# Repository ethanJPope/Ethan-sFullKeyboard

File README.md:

# Full Keyboard

My keybaord is a 100% version with a hotswappable pcb with custom USB_C Daughter Board PCB. 

## Why I made this Project
- I want a finished project
- Learn how to make a complex pcb
- Make a full and finished CAD Project

## PCB

**Keyboard PCB**

**USB_C DAUGHTER BOARD**

## CAD

## Final Product

## BOM

| Item | Description         | Unit Price | Supplier   |
|------|---------------------|------------|------------|
| 1    | Custom Keyboard PCB | $55.82     | JLCPCB     |
| 2    | PCB Components      | $22.54     | LCSC       |
| 3    | USB-C Cable         | $6.23      | AliExpress |
| 4    | Hot Swap Sockets    | $6.90      | AliExpress |
| 5    | Stabilizers         | $5.97      | AliExpress |
| 6    | Switches            | $21.65     | AliExpress |
| 7    | Poron Foam          | $5.70      | AliExpress |
| 8    | Keycaps Set         | $19.99     | Amazon     |

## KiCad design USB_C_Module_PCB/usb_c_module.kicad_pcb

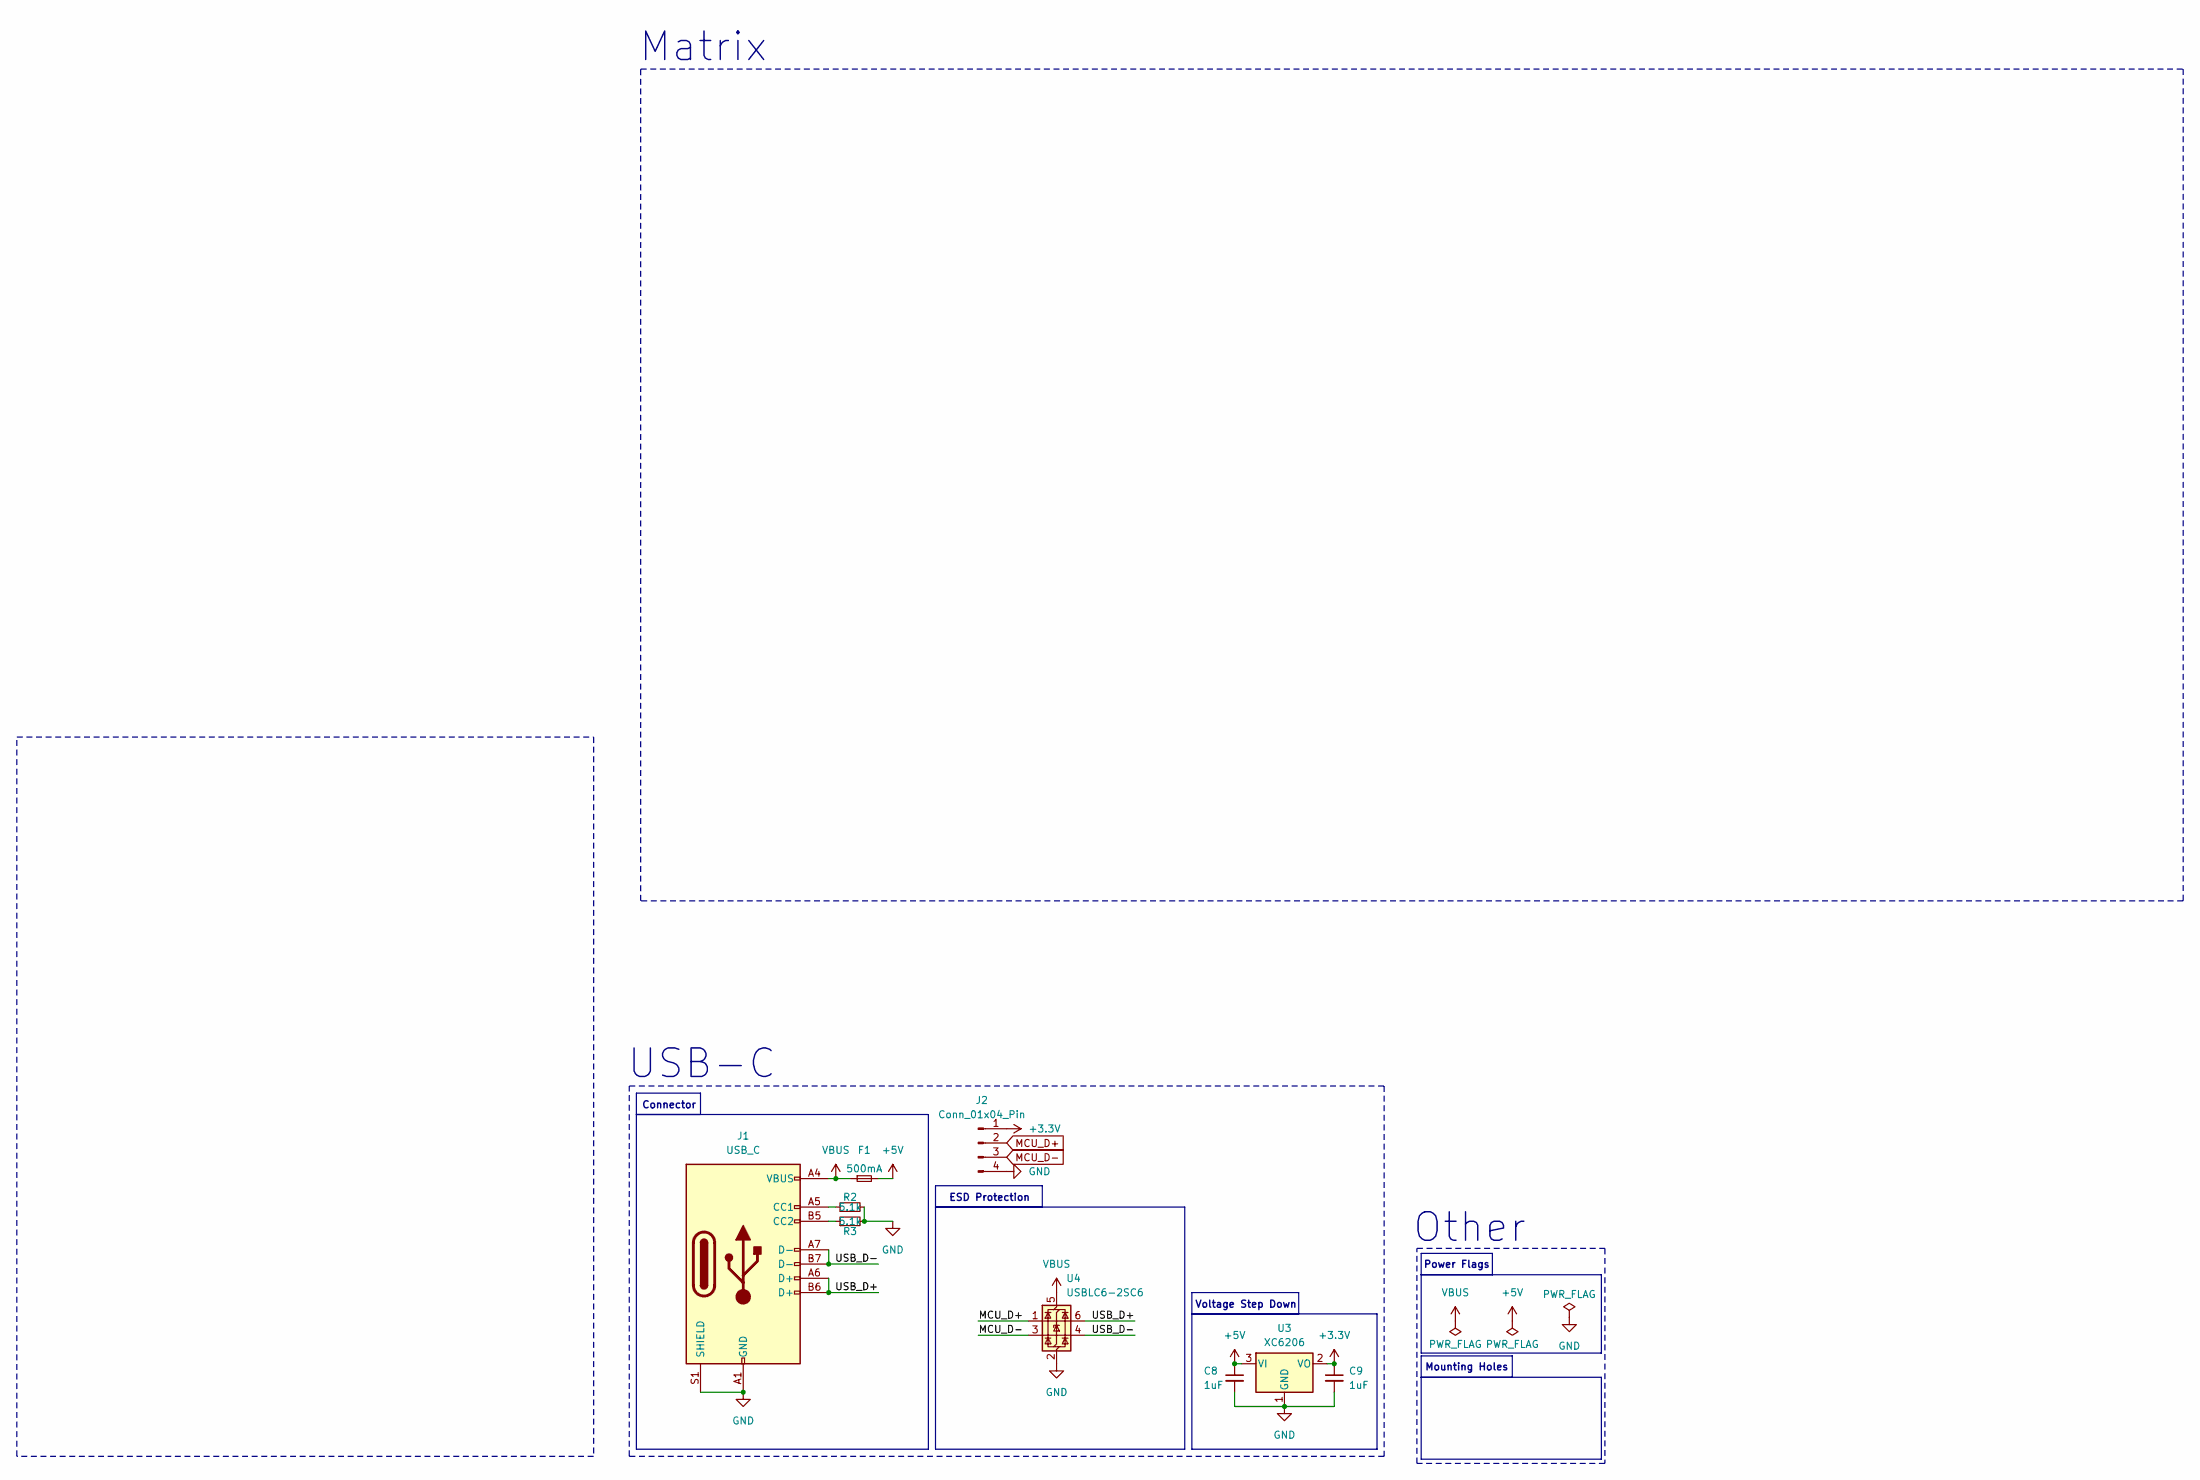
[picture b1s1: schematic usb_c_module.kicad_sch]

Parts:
C8, C9: 1uF; Capacitor_0402; LCSC C52923
F1: 500mA; Fuse_0603; LCSC C210357
J1: USB_C; USB_C_HRO_TYPE-C-31-M-12; LCSC C165948
J2: Conn_01x04_Pin; JST_EH_B4B-EH-A_1x04_P2.50mm_Vertical
R2, R3: 5.1k; Resistor_0402; LCSC C25905
U3: XC6206; Voltage_SOT-23; LCSC C5446
U4: USBLC6-2SC6; ESD_SOT-23-6; LCSC C2827654

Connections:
+3.3V: C9.1, J2.1, U3.2 (VO)
+5V: C8.1, F1.2, U3.3 (VI)
/USB_D+: J1.A6 (D+), J1.B6 (D+), U4.6 (I/O1)
/USB_D-: J1.A7 (D-), J1.B7 (D-), U4.4 (I/O2)
GND: C8.2, C9.2, J1.A1 (GND), J1.A12 (GND), J1.B1 (GND), J1.B12 (GND), J1.S1 (SHIELD), J2.4, R2.2, R3.2, U3.1 (GND), U4.2 (GND)
MCU_D+: J2.2, U4.1 (I/O1)
MCU_D-: J2.3, U4.3 (I/O2)
unnamed: J1.A5 (CC1), R2.1
unnamed: J1.B5 (CC2), R3.1
VBUS: F1.1, J1.A4 (VBUS), J1.A9 (VBUS), J1.B4 (VBUS), J1.B9 (VBUS), U4.5 (VBUS)

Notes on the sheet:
USB-C
Mounting Holes
ESD Protection
Power Flags
Voltage Step Down
Other
Matrix
Connector

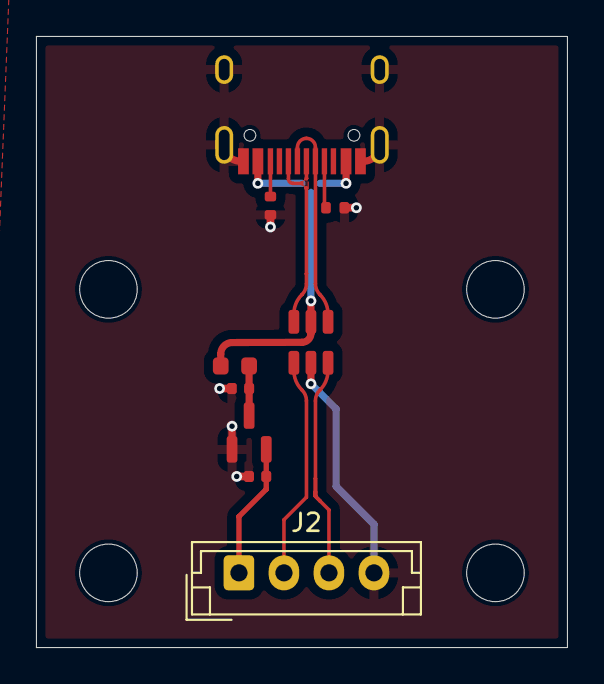
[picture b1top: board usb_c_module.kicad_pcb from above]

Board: 4 copper layers, 29.5 x 34.0 mm, 9 parts (0 on the bottom side), 10 nets.

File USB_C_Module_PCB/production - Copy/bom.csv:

Designator,Footprint,Quantity,Value,LCSC Part #
"C8, C9",Capacitor_0402,2,1uF,C52923
F1,Fuse_0603,1,500mA,C210357
J1,USB_C_HRO_TYPE-C-31-M-12,1,USB_C,C165948
J2,JST_EH_B4B-EH-A_1x04_P2.50mm_Vertical,1,Conn_01x04_Pin,
"R2, R3",Resistor_0402,2,5.1k,C25905
U3,Voltage_SOT-23,1,XC6206,C5446
U4,ESD_SOT-23-6,1,USBLC6-2SC6,C2827654

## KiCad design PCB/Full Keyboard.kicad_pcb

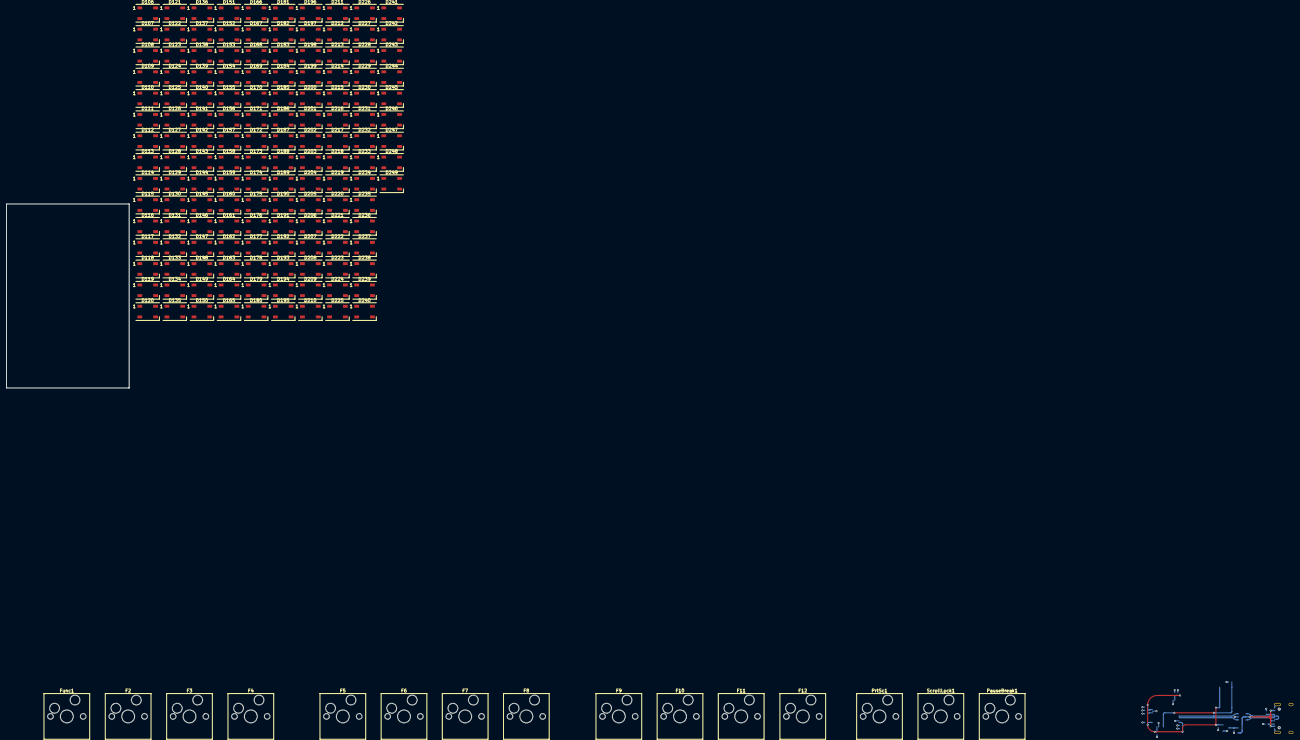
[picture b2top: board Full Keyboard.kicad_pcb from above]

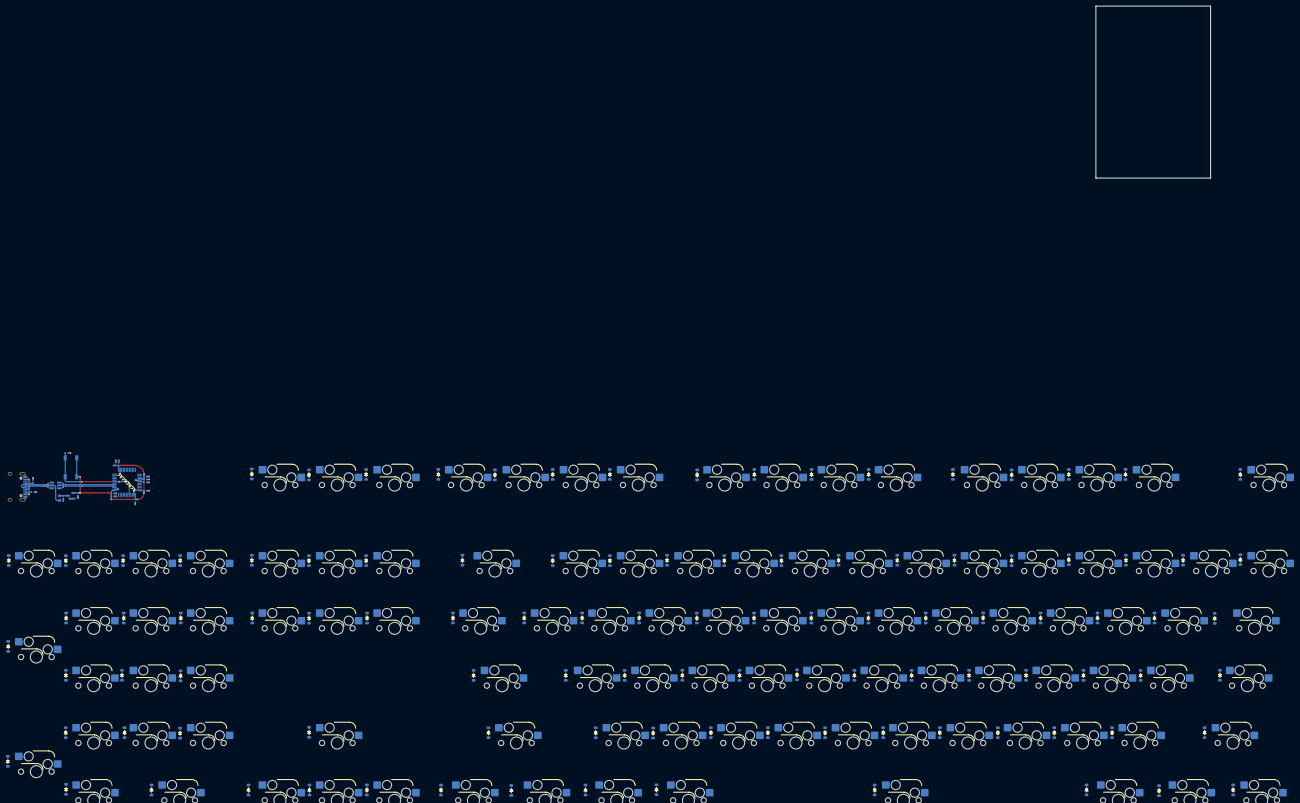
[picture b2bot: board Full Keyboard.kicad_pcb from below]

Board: 4 copper layers, 372 parts (124 on the bottom side), 286 nets.

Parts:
"0"1, "1, "1"1, "2"1, "3"1, "4"1, "5"1, "6"1, "7"1, "8"1, "9"1: Keyswitch; Hotswap_MX_1.00u
"-"1: Keyswitch; Hotswap_MX_1.00u
"="1: Keyswitch; Hotswap_MX_1.00u
"?"1: Keyswitch; Hotswap_MX_1.00u
;1: Keyswitch; Hotswap_MX_1.00u
<1: Keyswitch; Hotswap_MX_1.00u
>1: Keyswitch; Hotswap_MX_1.00u
A1: Keyswitch; Hotswap_MX_1.00u
B1: Keyswitch; Hotswap_MX_1.00u
Backspace1: Keyswitch; Hotswap_MX_2.00u
C1: Keyswitch; Hotswap_MX_1.00u
C7, C10, C11, C13, C16: 100nF; Capacitor_0402
C8, C9, C15: 1uF; Capacitor_0402
C12, C17: 4.7uF; Capacitor_0402
C14: 10nF; Capacitor_0402
CapsLock1: Keyswitch; Hotswap_MX_1.75u
D1, D2, D3, D4, D5, D6, D7, D8, D9, D10, D11, D12, D13, D14, D15, D16, D17, D18, D19, D20, D21, D22, D23, D24, D25, D26, D27, D28, D29, D30, D31, D32, D33, D34, D35, D36, D37, D38, D39, D40, D41, D42, D43, D44, D45, D46, D47, D48, D49, D50, D51, D52, D53, D54, D55, D56, D57, D58, D59, D60, D61, D62, D63, D64, D65, D66, D67, D68, D69, D70, D71, D72, D73, D74, D75, D76, D77, D78, D79, D80, D81, D82, D83, D84, D85, D86, D87, D88, D89, D90, D91, D92, D93, D94, D95, D96, D97, D98, D99, D100, D101, D102, D103, D104: Diode; Diode_SOD-123
D105: Keyswitch; Hotswap_MX_1.00u
D106, D107, D108, D109, D110, D111, D112, D113, D114, D115, D116, D117, D118, D119, D120, D121, D122, D123, D124, D125, D126, D127, D128, D129, D130, D131, D132, D133, D134, D135, D136, D137, D138, D139, D140, D141, D142, D143, D144, D145, D146, D147, D148, D149, D150, D151, D152, D153, D154, D155, D156, D157, D158, D159, D160, D161, D162, D163, D164, D165, D166, D167, D168, D169, D170, D171, D172, D173, D174, D175, D176, D177, D178, D179, D180, D181, D182, D183, D184, D185, D186, D187, D188, D189, D190, D191, D192, D193, D194, D195, D196, D197, D198, D199, D200, D201, D202, D203, D204, D205, D206, D207, D208, D209, D210, D211, D212, D213, D214, D215, D216, D217, D218, D219, D220, D221, D222, D223, D224, D225, D226, D227, D228, D229, D230, D231, D232, D233, D234, D235, D236, D237, D238, D239, D240, D241, D242, D243, D244, D245, D246, D247, D248, D249: LED_WS2812B
Delete1: Keyswitch; Hotswap_MX_1.00u
DownArrow1: Keyswitch; Hotswap_MX_1.00u
E1: Keyswitch; Hotswap_MX_1.00u
ESC1: Keyswitch; Hotswap_MX_1.00u
End1: Keyswitch; Hotswap_MX_1.00u
Enter1: Keyswitch; Hotswap_MX_2.25u
F1: 500mA; Fuse_0603
F2, F3, F4, F5, F6, F7, F8, F9, F10, F11, F12, F13: Keyswitch; Hotswap_MX_1.00u
Func1: Keyswitch; Hotswap_MX_1.00u
G1: Keyswitch; Hotswap_MX_1.00u
H1: Keyswitch; Hotswap_MX_1.00u
Home1: Keyswitch; Hotswap_MX_1.00u
I1: Keyswitch; Hotswap_MX_1.00u
Insert1: Keyswitch; Hotswap_MX_1.00u
J1: USB_C; USB_C_HRO_TYPE-C-31-M-12
J2: Keyswitch; Hotswap_MX_1.00u
K1: Keyswitch; Hotswap_MX_1.00u
L1: Keyswitch; Hotswap_MX_1.00u
LeftAlt1: Keyswitch; Hotswap_MX_1.25u
LeftArrow1: Keyswitch; Hotswap_MX_1.00u
LeftControl1: Keyswitch; Hotswap_MX_1.25u
LeftWin1: Keyswitch; Hotswap_MX_1.25u
M1: Keyswitch; Hotswap_MX_1.00u
Menu1: Keyswitch; Hotswap_MX_1.25u
N1: Keyswitch; Hotswap_MX_1.00u
Num0: Keyswitch; Hotswap_MX_2.00u
Num1, Num2, Num3, Num4, Num5, Num6, Num7, Num8, Num9, Num.1: Keyswitch; Hotswap_MX_1.00u
Num*1: Keyswitch; Hotswap_MX_1.00u
Num+1: Keyswitch; Hotswap_MX_2.00u_90deg
Num-1: Keyswitch; Hotswap_MX_1.00u
Num/1: Keyswitch; Hotswap_MX_1.00u
NumEnter1: Keyswitch; Hotswap_MX_2.00u_90deg
NumLock1: Keyswitch; Hotswap_MX_1.00u
O1: Keyswitch; Hotswap_MX_1.00u
P1: Keyswitch; Hotswap_MX_1.00u
PauseBreak1: Keyswitch; Hotswap_MX_1.00u
PgDn1: Keyswitch; Hotswap_MX_1.00u
PgUp1: Keyswitch; Hotswap_MX_1.00u
PrtSc1: Keyswitch; Hotswap_MX_1.00u
Q1: Keyswitch; Hotswap_MX_1.00u
R1: 10k; Resistor_0402
R2, R3: 5.1k; Resistor_0402
R4: Keyswitch; Hotswap_MX_1.00u
RightAlt1: Keyswitch; Hotswap_MX_1.25u
RightArrow1: Keyswitch; Hotswap_MX_1.00u
RightControl1: Keyswitch; Hotswap_MX_1.25u
RightShift1: Keyswitch; Hotswap_MX_2.75u
RightWin1: Keyswitch; Hotswap_MX_1.25u
S1: Keyswitch; Hotswap_MX_1.00u
SW1: SW_Push; Button_TL3342
ScrollLock1: Keyswitch; Hotswap_MX_1.00u
Shift1: Keyswitch; Hotswap_MX_2.25u
Space1: Keyswitch; Hotswap_MX_6.25u
T1: Keyswitch; Hotswap_MX_1.00u
Tab1: Keyswitch; Hotswap_MX_1.50u
Tilde1: Keyswitch; Hotswap_MX_1.00u
U1: STM32F072CBT6; Package_LQFP-48_7x7mm_P0.5
U2: Keyswitch; Hotswap_MX_1.00u
U3: XC6206; Voltage_SOT-23
U4: USBLC6-2SC6; ESD_SOT-23-6
UpArrow1: Keyswitch; Hotswap_MX_1.00u
V1: Keyswitch; Hotswap_MX_1.00u
W1: Keyswitch; Hotswap_MX_1.00u
X1: Keyswitch; Hotswap_MX_1.00u
Y1: Keyswitch; Hotswap_MX_1.00u
Z1: Keyswitch; Hotswap_MX_1.00u
\1: Keyswitch; Hotswap_MX_1.50u
{1: Keyswitch; Hotswap_MX_1.00u
}1: Keyswitch; Hotswap_MX_1.00u

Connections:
+3.3V: C9.1, C10.2, C11.2, C12.2, C13.2, C14.2, C15.2, C16.2, C17.2, SW1.1, U1.1 (VBAT), U1.9 (VDDA), U1.24 (VDD), U1.36 (VDDIO2), U1.48 (VDD), U3.2 (VO)
+5V: C8.1, D106.1 (VDD), D107.1 (VDD), D108.1 (VDD), D109.1 (VDD), D110.1 (VDD), D111.1 (VDD), D112.1 (VDD), D113.1 (VDD), D114.1 (VDD), D115.1 (VDD), D116.1 (VDD), D117.1 (VDD), D118.1 (VDD), D119.1 (VDD), D120.1 (VDD), D121.1 (VDD), D122.1 (VDD), D123.1 (VDD), D124.1 (VDD), D125.1 (VDD), D126.1 (VDD), D127.1 (VDD), D128.1 (VDD), D129.1 (VDD), D130.1 (VDD), D131.1 (VDD), D132.1 (VDD), D133.1 (VDD), D134.1 (VDD), D135.1 (VDD), D136.1 (VDD), D137.1 (VDD), D138.1 (VDD), D139.1 (VDD), D140.1 (VDD), D141.1 (VDD), D142.1 (VDD), D143.1 (VDD), D144.1 (VDD), D145.1 (VDD), D146.1 (VDD), D147.1 (VDD), D148.1 (VDD), D149.1 (VDD), D150.1 (VDD), D151.1 (VDD), D152.1 (VDD), D153.1 (VDD), D154.1 (VDD), D155.1 (VDD), D156.1 (VDD), D157.1 (VDD), D158.1 (VDD), D159.1 (VDD), D160.1 (VDD), D161.1 (VDD), D162.1 (VDD), D163.1 (VDD), D164.1 (VDD), D165.1 (VDD), D166.1 (VDD), D167.1 (VDD), D168.1 (VDD), D169.1 (VDD), D170.1 (VDD), D171.1 (VDD), D172.1 (VDD), D173.1 (VDD), D174.1 (VDD), D175.1 (VDD), D176.1 (VDD), D177.1 (VDD), D178.1 (VDD), D179.1 (VDD), D180.1 (VDD), D181.1 (VDD), D182.1 (VDD), D183.1 (VDD), D184.1 (VDD), D185.1 (VDD), D186.1 (VDD), D187.1 (VDD), D188.1 (VDD), D189.1 (VDD), D190.1 (VDD), D191.1 (VDD), D192.1 (VDD), D193.1 (VDD), D194.1 (VDD), D195.1 (VDD), D196.1 (VDD), D197.1 (VDD), D198.1 (VDD), D199.1 (VDD), D200.1 (VDD), D201.1 (VDD), D202.1 (VDD), D203.1 (VDD), D204.1 (VDD), D205.1 (VDD), D206.1 (VDD), D207.1 (VDD), D208.1 (VDD), D209.1 (VDD), D210.1 (VDD), D211.1 (VDD), D212.1 (VDD), D213.1 (VDD), D214.1 (VDD), D215.1 (VDD), D216.1 (VDD), D217.1 (VDD), D218.1 (VDD), D219.1 (VDD), D220.1 (VDD), D221.1 (VDD), D222.1 (VDD), D223.1 (VDD), D224.1 (VDD), D225.1 (VDD), D226.1 (VDD), D227.1 (VDD), D228.1 (VDD), D229.1 (VDD), D230.1 (VDD), D231.1 (VDD), D232.1 (VDD), D233.1 (VDD), D234.1 (VDD), D235.1 (VDD), D236.1 (VDD), D237.1 (VDD), D238.1 (VDD), D239.1 (VDD), D240.1 (VDD), D241.1 (VDD), D242.1 (VDD), D243.1 (VDD), D244.1 (VDD), D245.1 (VDD), D246.1 (VDD), D247.1 (VDD), D248.1 (VDD), D249.1 (VDD), F1.2, U3.3 (VI)
/BOOT0: R1.2, SW1.2, U1.44 (BOOT0)
/MCU_D+: U1.33 (PA12), U4.1 (I/O1)
/MCU_D-: U1.32 (PA11), U4.3 (I/O2)
/NRST: C7.1, U1.7 (NRST)
/USB_D+: J1.A6 (D+), J1.B6 (D+), U4.6 (I/O1)
/USB_D-: J1.A7 (D-), J1.B7 (D-), U4.4 (I/O2)
Col0: CapsLock1.1, ESC1.1, LeftControl1.1, Shift1.1, Tab1.1, Tilde1.1
Col1: "1"1.1, A1.1, Func1.1, LeftWin1.1, Q1.1, Z1.1
Col2: "2"1.1, F2.1, LeftAlt1.1, S1.1, W1.1, X1.1
Col3: "3"1.1, C1.1, D105.1, E1.1, F3.1
Col4: "4"1.1, F4.1, F13.1, R4.1, V1.1
Col5: "5"1.1, B1.1, F5.1, G1.1, Space1.1, T1.1
Col6: "6"1.1, F6.1, H1.1, N1.1, Y1.1
Col7: "7"1.1, F7.1, J2.1, M1.1, U2.1
Col8: "8"1.1, <1.1, F8.1, I1.1, K1.1
Col9: "9"1.1, >1.1, F9.1, L1.1, O1.1, RightAlt1.1
Col10: "0"1.1, "?"1.1, ;1.1, F10.1, P1.1, RightWin1.1
Col11: "1.1, "-"1.1, F11.1, Menu1.1, RightShift1.1, {1.1
Col12: "="1.1, Enter1.1, F12.1, }1.1
Col13: Backspace1.1, RightControl1.1, \1.1
Col14: Delete1.1, Insert1.1, LeftArrow1.1, PrtSc1.1
Col15: DownArrow1.1, End1.1, Home1.1, ScrollLock1.1, UpArrow1.1
Col16: PauseBreak1.1, PgDn1.1, PgUp1.1, RightArrow1.1
Col17: Num0.1, Num1.1, Num4.1, Num7.1, NumLock1.1
Col18: Num2.1, Num5.1, Num8.1, Num/1.1
Col19: Num3.1, Num6.1, Num9.1, Num*1.1, Num.1.1
Col20: Num+1.1, Num-1.1, NumEnter1.1
GND: C7.2, C8.2, C9.2, C10.1, C11.1, C12.1, C13.1, C14.1, C15.1, C16.1, C17.1, D106.3 (VSS), D107.3 (VSS), D108.3 (VSS), D109.3 (VSS), D110.3 (VSS), D111.3 (VSS), D112.3 (VSS), D113.3 (VSS), D114.3 (VSS), D115.3 (VSS), D116.3 (VSS), D117.3 (VSS), D118.3 (VSS), D119.3 (VSS), D120.3 (VSS), D121.3 (VSS), D122.3 (VSS), D123.3 (VSS), D124.3 (VSS), D125.3 (VSS), D126.3 (VSS), D127.3 (VSS), D128.3 (VSS), D129.3 (VSS), D130.3 (VSS), D131.3 (VSS), D132.3 (VSS), D133.3 (VSS), D134.3 (VSS), D135.3 (VSS), D136.3 (VSS), D137.3 (VSS), D138.3 (VSS), D139.3 (VSS), D140.3 (VSS), D141.3 (VSS), D142.3 (VSS), D143.3 (VSS), D144.3 (VSS), D145.3 (VSS), D146.3 (VSS), D147.3 (VSS), D148.3 (VSS), D149.3 (VSS), D150.3 (VSS), D151.3 (VSS), D152.3 (VSS), D153.3 (VSS), D154.3 (VSS), D155.3 (VSS), D156.3 (VSS), D157.3 (VSS), D158.3 (VSS), D159.3 (VSS), D160.3 (VSS), D161.3 (VSS), D162.3 (VSS), D163.3 (VSS), D164.3 (VSS), D165.3 (VSS), D166.3 (VSS), D167.3 (VSS), D168.3 (VSS), D169.3 (VSS), D170.3 (VSS), D171.3 (VSS), D172.3 (VSS), D173.3 (VSS), D174.3 (VSS), D175.3 (VSS), D176.3 (VSS), D177.3 (VSS), D178.3 (VSS), D179.3 (VSS), D180.3 (VSS), D181.3 (VSS), D182.3 (VSS), D183.3 (VSS), D184.3 (VSS), D185.3 (VSS), D186.3 (VSS), D187.3 (VSS), D188.3 (VSS), D189.3 (VSS), D190.3 (VSS), D191.3 (VSS), D192.3 (VSS), D193.3 (VSS), D194.3 (VSS), D195.3 (VSS), D196.3 (VSS), D197.3 (VSS), D198.3 (VSS), D199.3 (VSS), D200.3 (VSS), D201.3 (VSS), D202.3 (VSS), D203.3 (VSS), D204.3 (VSS), D205.3 (VSS), D206.3 (VSS), D207.3 (VSS), D208.3 (VSS), D209.3 (VSS), D210.3 (VSS), D211.3 (VSS), D212.3 (VSS), D213.3 (VSS), D214.3 (VSS), D215.3 (VSS), D216.3 (VSS), D217.3 (VSS), D218.3 (VSS), D219.3 (VSS), D220.3 (VSS), D221.3 (VSS), D222.3 (VSS), D223.3 (VSS), D224.3 (VSS), D225.3 (VSS), D226.3 (VSS), D227.3 (VSS), D228.3 (VSS), D229.3 (VSS), D230.3 (VSS), D231.3 (VSS), D232.3 (VSS), D233.3 (VSS), D234.3 (VSS), D235.3 (VSS), D236.3 (VSS), D237.3 (VSS), D238.3 (VSS), D239.3 (VSS), D240.3 (VSS), D241.3 (VSS), D242.3 (VSS), D243.3 (VSS), D244.3 (VSS), D245.3 (VSS), D246.3 (VSS), D247.3 (VSS), D248.3 (VSS), D249.3 (VSS), J1.A1 (GND), J1.A12 (GND), J1.B1 (GND), J1.B12 (GND), J1.S1 (SHIELD), R1.1, R2.2, R3.2, U1.8 (VSSA), U1.23 (VSS), U1.35 (VSS), U1.47 (VSS), U3.1 (GND), U4.2 (GND)
unnamed: D1.2 (A), ESC1.2
unnamed: D2.2 (A), Func1.2
unnamed: D3.2 (A), F2.2
unnamed: D4.2 (A), F3.2
unnamed: D5.2 (A), F4.2
unnamed: D6.2 (A), F5.2
unnamed: D7.2 (A), F6.2
unnamed: D8.2 (A), F7.2
unnamed: D9.2 (A), F8.2
unnamed: D10.2 (A), F9.2
unnamed: D11.2 (A), F10.2
unnamed: D12.2 (A), F11.2
unnamed: D13.2 (A), PrtSc1.2
unnamed: D14.2 (A), ScrollLock1.2
unnamed: D15.2 (A), PauseBreak1.2
unnamed: D16.2 (A), F12.2
unnamed: D17.2 (A), Tilde1.2
unnamed: "1"1.2, D18.2 (A)
unnamed: "2"1.2, D19.2 (A)
unnamed: "3"1.2, D20.2 (A)
unnamed: "4"1.2, D21.2 (A)
unnamed: "5"1.2, D22.2 (A)
unnamed: "6"1.2, D23.2 (A)
unnamed: "7"1.2, D24.2 (A)
unnamed: "8"1.2, D25.2 (A)
unnamed: "9"1.2, D26.2 (A)
unnamed: "0"1.2, D27.2 (A)
unnamed: "-"1.2, D28.2 (A)
unnamed: "="1.2, D29.2 (A)
unnamed: Backspace1.2, D30.2 (A)
unnamed: D31.2 (A), Insert1.2
unnamed: D32.2 (A), Home1.2
unnamed: D33.2 (A), PgUp1.2
unnamed: D34.2 (A), NumLock1.2
unnamed: D35.2 (A), Num/1.2
unnamed: D36.2 (A), Num*1.2
unnamed: D37.2 (A), Num-1.2
unnamed: D38.2 (A), Tab1.2
unnamed: D39.2 (A), Q1.2
unnamed: D40.2 (A), W1.2
unnamed: D41.2 (A), E1.2
unnamed: D42.2 (A), R4.2
unnamed: D43.2 (A), T1.2
unnamed: D44.2 (A), Y1.2
unnamed: D45.2 (A), U2.2
unnamed: D46.2 (A), I1.2
unnamed: D47.2 (A), O1.2
unnamed: D48.2 (A), P1.2
unnamed: D49.2 (A), {1.2
unnamed: D50.2 (A), }1.2
unnamed: D51.2 (A), \1.2
unnamed: D52.2 (A), Delete1.2
unnamed: D53.2 (A), End1.2
unnamed: D54.2 (A), PgDn1.2
unnamed: D55.2 (A), Num7.2
unnamed: D56.2 (A), Num8.2
unnamed: D57.2 (A), Num9.2
unnamed: D58.2 (A), Num+1.2
unnamed: CapsLock1.2, D59.2 (A)
unnamed: A1.2, D60.2 (A)
unnamed: D61.2 (A), S1.2
unnamed: D62.2 (A), D105.2
unnamed: D63.2 (A), F13.2
unnamed: D64.2 (A), G1.2
unnamed: D65.2 (A), H1.2
unnamed: D66.2 (A), J2.2
unnamed: D67.2 (A), K1.2
unnamed: D68.2 (A), L1.2
unnamed: ;1.2, D69.2 (A)
unnamed: "1.2, D70.2 (A)
unnamed: D71.2 (A), Enter1.2
unnamed: D72.2 (A), Num5.2
unnamed: D73.2 (A), Num6.2
unnamed: D74.2 (A), Num4.2
unnamed: D75.2 (A), Shift1.2
unnamed: D76.2 (A), Z1.2
unnamed: D77.2 (A), X1.2
unnamed: C1.2, D78.2 (A)
unnamed: D79.2 (A), V1.2
unnamed: B1.2, D80.2 (A)
unnamed: D81.2 (A), N1.2
unnamed: D82.2 (A), M1.2
unnamed: <1.2, D83.2 (A)
unnamed: >1.2, D84.2 (A)
unnamed: "?"1.2, D85.2 (A)
unnamed: D86.2 (A), RightShift1.2
unnamed: D87.2 (A), UpArrow1.2
unnamed: D88.2 (A), Num1.2
unnamed: D89.2 (A), Num2.2
unnamed: D90.2 (A), Num3.2
unnamed: D91.2 (A), NumEnter1.2
unnamed: D92.2 (A), LeftControl1.2
unnamed: D93.2 (A), LeftWin1.2
unnamed: D94.2 (A), LeftAlt1.2
unnamed: D95.2 (A), Space1.2
unnamed: D96.2 (A), RightAlt1.2
unnamed: D97.2 (A), RightWin1.2
unnamed: D98.2 (A), Menu1.2
unnamed: D99.2 (A), RightControl1.2
unnamed: D100.2 (A), LeftArrow1.2
unnamed: D101.2 (A), DownArrow1.2
unnamed: D102.2 (A), RightArrow1.2
unnamed: D103.2 (A), Num0.2
unnamed: D104.2 (A), Num.1.2
unnamed: D106.2 (DOUT), D107.4 (DIN)
unnamed: D107.2 (DOUT), D108.4 (DIN)
unnamed: D108.2 (DOUT), D109.4 (DIN)
unnamed: D109.2 (DOUT), D110.4 (DIN)
unnamed: D110.2 (DOUT), D111.4 (DIN)
unnamed: D111.2 (DOUT), D112.4 (DIN)
unnamed: D112.2 (DOUT), D113.4 (DIN)
unnamed: D113.2 (DOUT), D114.4 (DIN)
unnamed: D114.2 (DOUT), D115.4 (DIN)
unnamed: D115.2 (DOUT), D116.4 (DIN)
unnamed: D116.2 (DOUT), D117.4 (DIN)
unnamed: D117.2 (DOUT), D178.4 (DIN)
unnamed: D118.4 (DIN), D139.2 (DOUT)
unnamed: D118.2 (DOUT), D119.4 (DIN)
unnamed: D119.2 (DOUT), D120.4 (DIN)
unnamed: D120.2 (DOUT), D121.4 (DIN)
unnamed: D121.2 (DOUT), D122.4 (DIN)
unnamed: D122.2 (DOUT), D123.4 (DIN)
unnamed: D123.2 (DOUT), D124.4 (DIN)
unnamed: D124.2 (DOUT), D125.4 (DIN)
unnamed: D125.2 (DOUT), D126.4 (DIN)
unnamed: D126.2 (DOUT), D127.4 (DIN)
unnamed: D127.2 (DOUT), D140.4 (DIN)
unnamed: D128.4 (DIN), D179.2 (DOUT)
unnamed: D128.2 (DOUT), D129.4 (DIN)
unnamed: D129.2 (DOUT), D130.4 (DIN)
unnamed: D130.2 (DOUT), D131.4 (DIN)
unnamed: D131.2 (DOUT), D132.4 (DIN)
unnamed: D132.2 (DOUT), D133.4 (DIN)
unnamed: D133.2 (DOUT), D134.4 (DIN)
unnamed: D134.2 (DOUT), D135.4 (DIN)
unnamed: D135.2 (DOUT), D136.4 (DIN)
unnamed: D136.2 (DOUT), D137.4 (DIN)
unnamed: D137.2 (DOUT), D138.4 (DIN)
unnamed: D138.2 (DOUT), D139.4 (DIN)
unnamed: D140.2 (DOUT), D141.4 (DIN)
unnamed: D141.2 (DOUT), D180.4 (DIN)
unnamed: D142.4 (DIN), D181.2 (DOUT)
unnamed: D142.2 (DOUT), D143.4 (DIN)
unnamed: D143.2 (DOUT), D144.4 (DIN)
unnamed: D144.2 (DOUT), D145.4 (DIN)
unnamed: D145.2 (DOUT), D146.4 (DIN)
unnamed: D146.2 (DOUT), D147.4 (DIN)
unnamed: D147.2 (DOUT), D148.4 (DIN)
unnamed: D148.2 (DOUT), D149.4 (DIN)
unnamed: D149.2 (DOUT), D150.4 (DIN)
unnamed: D150.2 (DOUT), D151.4 (DIN)
unnamed: D151.2 (DOUT), D152.4 (DIN)
unnamed: D152.2 (DOUT), D153.4 (DIN)
unnamed: D153.2 (DOUT), D154.4 (DIN)
unnamed: D154.2 (DOUT), D155.4 (DIN)
unnamed: D155.2 (DOUT), D156.4 (DIN)
unnamed: D156.2 (DOUT), D157.4 (DIN)
unnamed: D157.2 (DOUT), D158.4 (DIN)
unnamed: D158.2 (DOUT), D159.4 (DIN)
unnamed: D159.2 (DOUT), D160.4 (DIN)
unnamed: D160.2 (DOUT), D161.4 (DIN)
unnamed: D161.2 (DOUT), D162.4 (DIN)
unnamed: D162.2 (DOUT), D163.4 (DIN)
unnamed: D163.2 (DOUT), D164.4 (DIN)
unnamed: D164.2 (DOUT), D165.4 (DIN)
unnamed: D165.2 (DOUT), D182.4 (DIN)
unnamed: D166.4 (DIN), D183.2 (DOUT)
unnamed: D166.2 (DOUT), D167.4 (DIN)
unnamed: D167.2 (DOUT), D168.4 (DIN)
unnamed: D168.2 (DOUT), D169.4 (DIN)
unnamed: D169.2 (DOUT), D170.4 (DIN)
unnamed: D170.2 (DOUT), D171.4 (DIN)
unnamed: D171.2 (DOUT), D172.4 (DIN)
unnamed: D172.2 (DOUT), D173.4 (DIN)
unnamed: D173.2 (DOUT), D174.4 (DIN)
unnamed: D174.2 (DOUT), D175.4 (DIN)
unnamed: D175.2 (DOUT), D176.4 (DIN)
unnamed: D176.2 (DOUT), D177.4 (DIN)
unnamed: D178.2 (DOUT), D184.4 (DIN)
unnamed: D179.4 (DIN), D185.2 (DOUT)
unnamed: D180.2 (DOUT), D186.4 (DIN)
unnamed: D181.4 (DIN), D187.2 (DOUT)
unnamed: D182.2 (DOUT), D188.4 (DIN)
unnamed: D183.4 (DIN), D189.2 (DOUT)
unnamed: D184.2 (DOUT), D190.4 (DIN)
unnamed: D185.4 (DIN), D191.2 (DOUT)
unnamed: D186.2 (DOUT), D192.4 (DIN)
unnamed: D187.4 (DIN), D193.2 (DOUT)
unnamed: D188.2 (DOUT), D194.4 (DIN)
unnamed: D189.4 (DIN), D195.2 (DOUT)
unnamed: D190.2 (DOUT), D196.4 (DIN)
unnamed: D191.4 (DIN), D197.2 (DOUT)
unnamed: D192.2 (DOUT), D198.4 (DIN)
unnamed: D193.4 (DIN), D199.2 (DOUT)
unnamed: D194.2 (DOUT), D200.4 (DIN)
unnamed: D195.4 (DIN), D201.2 (DOUT)
unnamed: D196.2 (DOUT), D202.4 (DIN)
unnamed: D197.4 (DIN), D203.2 (DOUT)
unnamed: D198.2 (DOUT), D204.4 (DIN)
unnamed: D199.4 (DIN), D205.2 (DOUT)
unnamed: D200.2 (DOUT), D206.4 (DIN)
unnamed: D201.4 (DIN), D207.2 (DOUT)
unnamed: D202.2 (DOUT), D208.4 (DIN)
unnamed: D203.4 (DIN), D209.2 (DOUT)
unnamed: D204.2 (DOUT), D210.4 (DIN)
unnamed: D205.4 (DIN), D211.2 (DOUT)
unnamed: D206.2 (DOUT), D212.4 (DIN)
unnamed: D207.4 (DIN), D213.2 (DOUT)
unnamed: D208.2 (DOUT), D214.4 (DIN)
unnamed: D209.4 (DIN), D215.2 (DOUT)
unnamed: D210.2 (DOUT), D216.4 (DIN)
unnamed: D211.4 (DIN), D217.2 (DOUT)
unnamed: D212.2 (DOUT), D218.4 (DIN)
unnamed: D213.4 (DIN), D219.2 (DOUT)
unnamed: D214.2 (DOUT), D220.4 (DIN)
unnamed: D215.4 (DIN), D221.2 (DOUT)
unnamed: D216.2 (DOUT), D222.4 (DIN)
unnamed: D217.4 (DIN), D223.2 (DOUT)
unnamed: D218.2 (DOUT), D224.4 (DIN)
unnamed: D219.4 (DIN), D225.2 (DOUT)
unnamed: D220.2 (DOUT), D226.4 (DIN)
unnamed: D221.4 (DIN), D227.2 (DOUT)
unnamed: D222.2 (DOUT), D228.4 (DIN)
unnamed: D223.4 (DIN), D229.2 (DOUT)
unnamed: D224.2 (DOUT), D230.4 (DIN)
unnamed: D225.4 (DIN), D231.2 (DOUT)
unnamed: D226.2 (DOUT), D232.4 (DIN)
unnamed: D227.4 (DIN), D233.2 (DOUT)
unnamed: D228.2 (DOUT), D234.4 (DIN)
unnamed: D229.4 (DIN), D235.2 (DOUT)
unnamed: D230.2 (DOUT), D236.4 (DIN)
unnamed: D231.4 (DIN), D237.2 (DOUT)
unnamed: D232.2 (DOUT), D238.4 (DIN)
unnamed: D233.4 (DIN), D239.2 (DOUT)
unnamed: D234.2 (DOUT), D240.4 (DIN)
unnamed: D235.4 (DIN), D241.2 (DOUT)
unnamed: D236.2 (DOUT), D242.4 (DIN)
unnamed: D237.4 (DIN), D243.2 (DOUT)
unnamed: D238.2 (DOUT), D244.4 (DIN)
unnamed: D239.4 (DIN), D245.2 (DOUT)
unnamed: D240.2 (DOUT), D246.4 (DIN)
unnamed: D241.4 (DIN), D247.2 (DOUT)
unnamed: D242.2 (DOUT), D248.4 (DIN)
unnamed: D243.4 (DIN), D249.2 (DOUT)
unnamed: D244.2 (DOUT), D245.4 (DIN)
unnamed: D246.2 (DOUT), D247.4 (DIN)
unnamed: D248.2 (DOUT), D249.4 (DIN)
unnamed: J1.A5 (CC1), R2.1
unnamed: J1.B5 (CC2), R3.1
Row0: D1.1 (K), D2.1 (K), D3.1 (K), D4.1 (K), D5.1 (K), D6.1 (K), D7.1 (K), D8.1 (K), D9.1 (K), D10.1 (K), D11.1 (K), D12.1 (K), D13.1 (K), D14.1 (K), D15.1 (K), D16.1 (K)
Row1: D17.1 (K), D18.1 (K), D19.1 (K), D20.1 (K), D21.1 (K), D22.1 (K), D23.1 (K), D24.1 (K), D25.1 (K), D26.1 (K), D27.1 (K), D28.1 (K), D29.1 (K), D30.1 (K), D31.1 (K), D32.1 (K), D33.1 (K), D34.1 (K), D35.1 (K), D36.1 (K), D37.1 (K)
Row2: D38.1 (K), D39.1 (K), D40.1 (K), D41.1 (K), D42.1 (K), D43.1 (K), D44.1 (K), D45.1 (K), D46.1 (K), D47.1 (K), D48.1 (K), D49.1 (K), D50.1 (K), D51.1 (K), D52.1 (K), D53.1 (K), D54.1 (K), D55.1 (K), D56.1 (K), D57.1 (K), D58.1 (K)
Row3: D59.1 (K), D60.1 (K), D61.1 (K), D62.1 (K), D63.1 (K), D64.1 (K), D65.1 (K), D66.1 (K), D67.1 (K), D68.1 (K), D69.1 (K), D70.1 (K), D71.1 (K), D72.1 (K), D73.1 (K), D74.1 (K)
Row4: D75.1 (K), D76.1 (K), D77.1 (K), D78.1 (K), D79.1 (K), D80.1 (K), D81.1 (K), D82.1 (K), D83.1 (K), D84.1 (K), D85.1 (K), D86.1 (K), D87.1 (K), D88.1 (K), D89.1 (K), D90.1 (K), D91.1 (K)
Row5: D92.1 (K), D93.1 (K), D94.1 (K), D95.1 (K), D96.1 (K), D97.1 (K), D98.1 (K), D99.1 (K), D100.1 (K), D101.1 (K), D102.1 (K), D103.1 (K), D104.1 (K)
VBUS: F1.1, J1.A4 (VBUS), J1.A9 (VBUS), J1.B4 (VBUS), J1.B9 (VBUS), U4.5 (VBUS)

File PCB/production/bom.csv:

Designator,Footprint,Quantity,Value,LCSC Part #
"""-""1, ""0""1, ""1, ""1""1, ""2""1, ""3""1, ""4""1, ""5""1, ""6""1, ""7""1, ""8""1, ""9""1, ""=""1, ""?""1, ;1, <1, >1, A1, B1, C1, D105, Delete1, DownArrow1, E1, ESC1, End1, F10, F11, F12, F13, F2, F3, F4, F5, F6, F7, F8, F9, Func1, G1, H1, Home1, I1, Insert1, J2, K1, L1, LeftArrow1, M1, N1, Num*1, Num-1, Num.1, Num/1, Num1, Num2, Num3, Num4, Num5, Num6, Num7, Num8, Num9, NumLock1, O1, P1, PauseBreak1, PgDn1, PgUp1, PrtSc1, Q1, R4, RightArrow1, S1, ScrollLock1, T1, Tilde1, U2, UpArrow1, V1, W1, X1, Y1, Z1, {1, }1",Hotswap_MX_1.00u,86,Keyswitch,
"Backspace1, Num0",Hotswap_MX_2.00u,2,Keyswitch,
"C10, C11, C13, C16, C7",Capacitor_0402,5,100nF,C307331
"C12, C17",Capacitor_0402,2,4.7uF,C23733
C14,Capacitor_0402,1,10nF,C15195
C15,Capacitor_0402,1,1uF,C52923
CapsLock1,Hotswap_MX_1.75u,1,Keyswitch,
"D1, D10, D100, D101, D102, D103, D104, D11, D12, D13, D14, D15, D16, D17, D18, D19, D2, D20, D21, D22, D23, D24, D25, D26, D27, D28, D29, D3, D30, D31, D32, D33, D34, D35, D36, D37, D38, D39, D4, D40, D41, D42, D43, D44, D45, D46, D47, D48, D49, D5, D50, D51, D52, D53, D54, D55, D56, D57, D58, D59, D6, D60, D61, D62, D63, D64, D65, D66, D67, D68, D69, D7, D70, D71, D72, D73, D74, D75, D76, D77, D78, D79, D8, D80, D81, D82, D83, D84, D85, D86, D87, D88, D89, D9, D90, D91, D92, D93, D94, D95, D96, D97, D98, D99",Diode_SOD-123,104,Diode,
"Enter1, Shift1",Hotswap_MX_2.25u,2,Keyswitch,
J3,JST_EH_B4B-EH-A_1x04_P2.50mm_Vertical,1,Conn_01x04_Pin,
"LeftAlt1, LeftControl1, LeftWin1, Menu1, RightAlt1, RightControl1, RightWin1",Hotswap_MX_1.25u,7,Keyswitch,
"Num+1, NumEnter1",Hotswap_MX_2.00u_90deg,2,Keyswitch,
R1,Resistor_0402,1,10k,C25744
RightShift1,Hotswap_MX_2.75u,1,Keyswitch,
SW1,Button_TL3342,1,SW_Push,C115351
Space1,Hotswap_MX_6.25u,1,Keyswitch,
"Tab1, \1",Hotswap_MX_1.50u,2,Keyswitch,
U1,Package_LQFP-48_7x7mm_P0.5,1,STM32F072CBT6,C81720

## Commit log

2025-06-04 First Push
2025-06-05 commit during highway call
2025-06-06 PCB Design
2025-06-12 push
2025-06-12 move
2025-07-26 code
